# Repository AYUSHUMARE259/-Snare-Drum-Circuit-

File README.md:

# Snare Drum Circuit — PCB Design (EE 322 AMSC Project)

**Course:** EE 322 – Analog and Mixed Signal Circuits
**Term:** Semester 1, 2025–26
**Team:** Team Behzad

## The Team

| Member | Roll No. |
|---|---|
| Yash Sonone | 23110318 |
| Sumedh Wankhede | 23110364 |
| Ayush Umare | 23110346 |

---

## What This Project Is

An electronic snare drum circuit, designed from schematic to soldered board and demonstrated live. The circuit synthesizes a snare-drum sound purely through analog circuitry — no samples, no microcontroller — and the final PCB played back an audible, recognizable snare hit.

Everything here was built the way a real hardware project should be: simulate first, prove it on a breadboard, then commit to copper.

## How We Got There

1. **Simulate** — Modeled the snare drum circuit in LTspice to confirm the topology would actually produce a snare-like waveform before touching hardware.
2. **Prototype** — Built the circuit on a breadboard to validate it worked with real components and real noise, not just an idealized simulation.
3. **Design the PCB** — Captured the schematic in KiCad, assigned footprints, ran ERC to catch wiring issues, then placed and routed the layout.
4. **Verify** — Ran DRC to check the layout against fabrication constraints, and reviewed the board in 3D before export.
5. **Fabricate** — Generated Gerber and drill files and sent them to LionsCircuit for manufacturing.
6. **Build & Demo** — Hand-soldered every component onto the fabricated board and demonstrated the finished circuit producing live snare drum audio.

---

## Repository Layout

```
├── Team_Behzad_Project_Proposal            # project proposal
├── full_schematic_kicad.kicad_pcb_final.kicad_pcb   # PCB layout (KiCad)
├── full_schematic_kicad.kicad_pcb_final.kicad_pro   # KiCad project file
├── gerber_files_amsc_project/                        # Fabrication-ready Gerbers
│   ├── *-F_Cu.gbr / *-B_Cu.gbr            # Copper layers (front/back)
│   ├── *-F_Mask.gbr / *-B_Mask.gbr        # Solder mask layers
│   ├── *-F_Silkscreen.gbr / *-B_Silkscreen.gbr  # Silkscreen layers
│   ├── *-Edge_Cuts.gbr                    # Board outline
│   ├── *-PTH.drl / *-NPTH.drl             # Drill files (plated/non-plated)
│   └── *-job.gbrjob                       # Gerber job file
└── Team Behzad_AMSC.pdf                              # Full written report
```

---

## Toolchain

- **LTspice** — pre-layout circuit simulation
- **KiCad** (v7+ recommended) — schematic capture and PCB layout
- **LionsCircuit** — PCB fabrication

## Getting the Project Running Locally

1. Install [KiCad](https://www.kicad.org/) (v7 or newer).
2. Clone the repo:
   ```bash
   git clone https://github.com/YOUR_USERNAME/Team-Behzad-AMSC.git
   ```
3. Open `full_schematic_kicad.kicad_pcb_final.kicad_pro` in KiCad to view the schematic and layout.

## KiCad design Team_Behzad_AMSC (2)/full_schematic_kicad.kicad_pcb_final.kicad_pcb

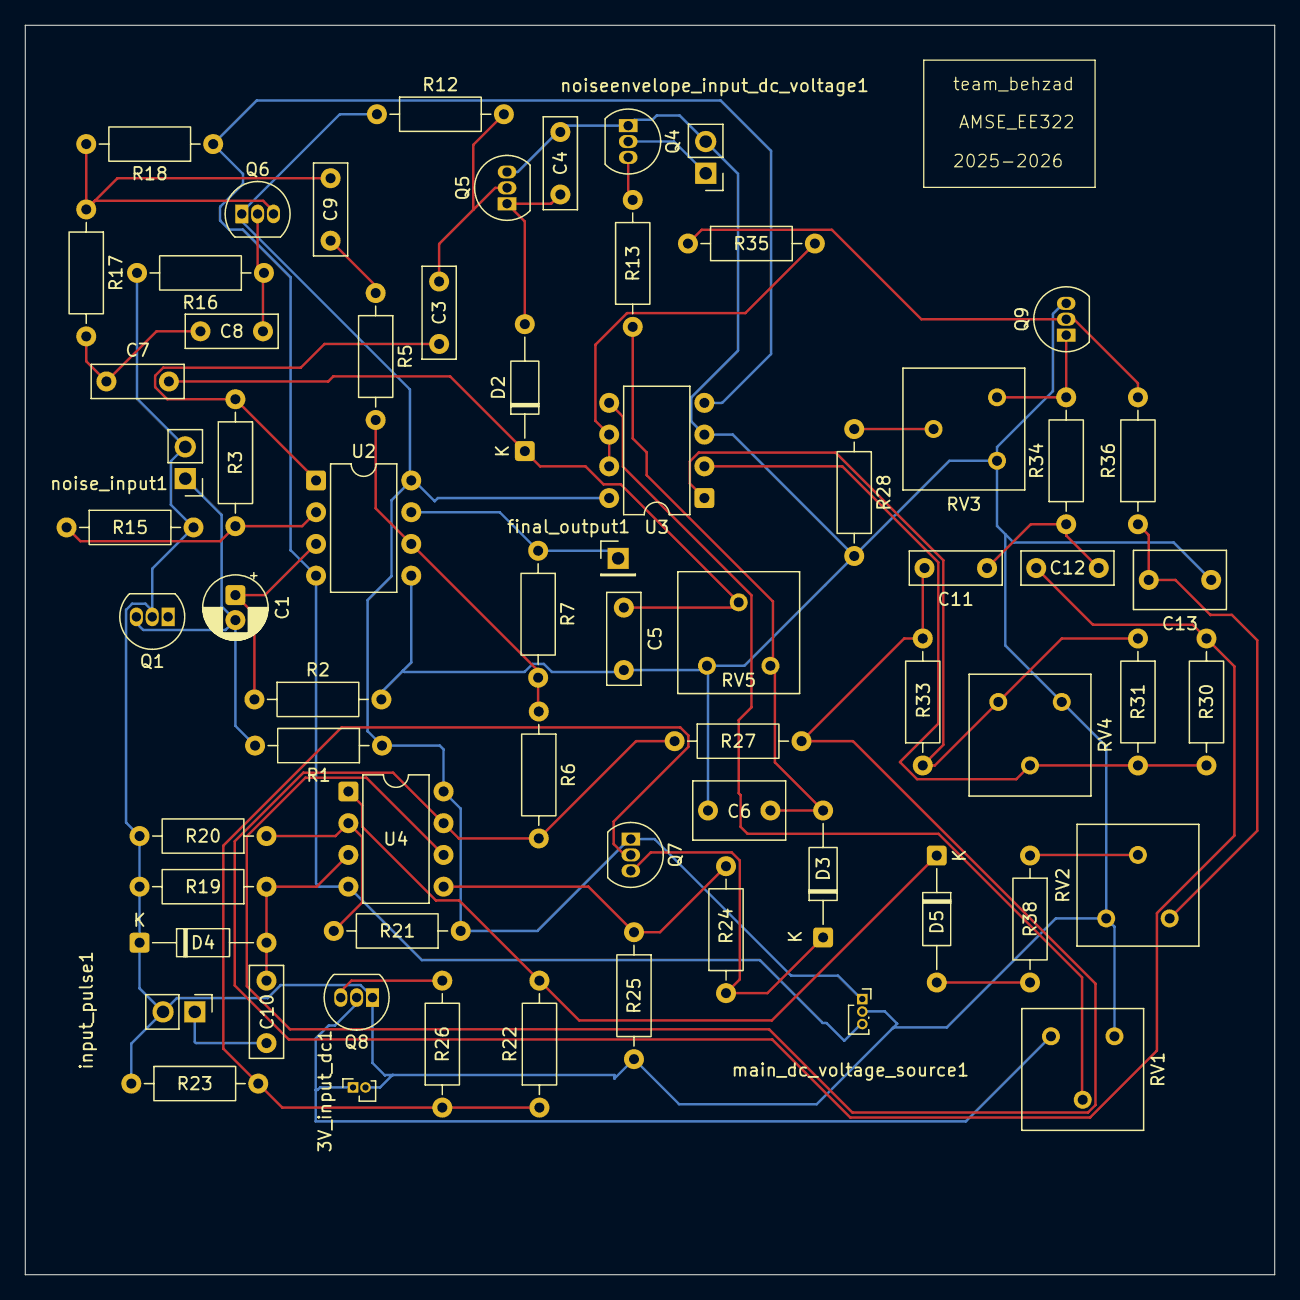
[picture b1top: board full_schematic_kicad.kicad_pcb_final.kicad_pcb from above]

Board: 2 copper layers, 100.0 x 100.0 mm, 66 parts (0 on the bottom side), 41 nets.

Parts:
3V_input_dc1: Conn_01x02_Socket; PinSocket_1x02_P1.00mm_Vertical
C1: 1µ; CP_Radial_D5.0mm_P2.00mm
C3, C11, C12: 33n; C_Rect_L7.2mm_W2.5mm_P5.00mm_FKS2_FKP2_MKS2_MKP2
C4, C5: 2.2n; C_Rect_L7.2mm_W2.5mm_P5.00mm_FKS2_FKP2_MKS2_MKP2
C6, C13: 470n; C_Rect_L7.2mm_W4.5mm_P5.00mm_FKS2_FKP2_MKS2_MKP2
C7, C8: 1n; C_Rect_L7.2mm_W2.5mm_P5.00mm_FKS2_FKP2_MKS2_MKP2
C9, C10: 10n; C_Rect_L7.2mm_W2.5mm_P5.00mm_FKS2_FKP2_MKS2_MKP2
D2, D3, D4, D5: D; D_DO-35_SOD27_P10.16mm_Horizontal
Q1, Q5, Q6, Q7, Q9: NPN; TO-92_Inline
Q4, Q8: PNP; TO-92_Inline
R1, R2, R6, R16, R21, R22: 100k; R_Axial_DIN0207_L6.3mm_D2.5mm_P10.16mm_Horizontal
R3, R12: 1Meg; R_Axial_DIN0207_L6.3mm_D2.5mm_P10.16mm_Horizontal
R5, R24: 10k; R_Axial_DIN0207_L6.3mm_D2.5mm_P10.16mm_Horizontal
R7, R20: 33k; R_Axial_DIN0207_L6.3mm_D2.5mm_P10.16mm_Horizontal
R13, R15, R17, R18, R26: 22k; R_Axial_DIN0207_L6.3mm_D2.5mm_P10.16mm_Horizontal
R19: 39k; R_Axial_DIN0207_L6.3mm_D2.5mm_P10.16mm_Horizontal
R23: 120k; R_Axial_DIN0207_L6.3mm_D2.5mm_P10.16mm_Horizontal
R25, R38: 1k; R_Axial_DIN0207_L6.3mm_D2.5mm_P10.16mm_Horizontal
R27: 910k; R_Axial_DIN0207_L6.3mm_D2.5mm_P10.16mm_Horizontal
R28: 470; R_Axial_DIN0207_L6.3mm_D2.5mm_P10.16mm_Horizontal
R30, R31, R35: 47k; R_Axial_DIN0207_L6.3mm_D2.5mm_P10.16mm_Horizontal
R33: 470k; R_Axial_DIN0207_L6.3mm_D2.5mm_P10.16mm_Horizontal
R34: 330; R_Axial_DIN0207_L6.3mm_D2.5mm_P10.16mm_Horizontal
R36: 27k; R_Axial_DIN0207_L6.3mm_D2.5mm_P10.16mm_Horizontal
RV1, RV2, RV3, RV4, RV5: R_Potentiometer; Potentiometer_Bourns_3386F_Vertical
U2, U3, U4: TL072; DIP-8_W7.62mm
final_output1: Conn_01x01_Socket; PinHeader_1x01_P2.54mm_Vertical
input_pulse1: Conn_01x02_Socket; PinHeader_1x02_P2.54mm_Vertical
main_dc_voltage_source1: Conn_01x03_Socket; PinSocket_1x03_P1.00mm_Vertical
noise_input1: Conn_01x02_Socket; PinHeader_1x02_P2.54mm_Vertical
noiseenvelope_input_dc_voltage1: Conn_01x02_Socket; PinHeader_1x02_P2.54mm_Vertical

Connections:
0: 3V_input_dc1.2, C4.1, C5.2, C6.2, C13.1, D4.1 (+), Q1.2 (B), Q4.1 (C), Q5.3 (E), Q8.1 (C), Q9.3 (E), R2.2, R15.2, R16.2, R19.2, R20.2, R23.1, R25.2, R28.2, RV1.3, RV2.3, RV3.3, RV4.3, RV5.3, U2.5 (+), U3.3 (+), input_pulse1.2, main_dc_voltage_source1.2, noise_input1.2, noiseenvelope_input_dc_voltage1.2
/3v: 3V_input_dc1.1, Q8.2 (B), RV1.1
/-vdd: R18.1, U2.4 (V-), U3.4 (V-), U4.4 (V-), main_dc_voltage_source1.3
/vdd: Q6.1 (C), Q7.1 (C), R1.1, R12.1, R21.1, U2.8 (V+), U3.8 (V+), U4.8 (V+), main_dc_voltage_source1.1
unnamed: C3.2, R3.1, U2.1
unnamed: C7.1, C8.2, R17.2
unnamed: C9.1, R5.1
unnamed: C11.1, C12.2, R34.1
unnamed: C12.1, R6.2, R27.1, R30.2, U4.7
unnamed: C13.2, R36.1, RV2.1
unnamed: C5.1, C7.2, D2.1 (+), RV5.2
unnamed: C4.2, D2.2 (-), Q5.1 (C)
unnamed: D3.1 (+), Q7.3 (E), R24.1
unnamed: C6.1, D3.2 (-), R13.1, RV5.1
unnamed: C10.1, D4.2 (-), R19.1, U4.3 (+)
unnamed: D5.1 (+), R22.2, U4.1
unnamed: D5.2 (-), R38.2
unnamed: C1.2, Q1.3 (E), R1.2, noise_input1.1
unnamed: Q4.2 (B), noiseenvelope_input_dc_voltage1.1
unnamed: Q4.3 (E), R13.2
unnamed: C3.1, Q5.2 (B), R12.2
unnamed: C8.1, Q6.2 (B), R16.1
unnamed: C9.2, Q6.3 (E), R17.1, R18.2
unnamed: Q7.2 (B), R22.1, R23.2, R26.1
unnamed: Q8.3 (E), R26.2
unnamed: Q9.2 (B), R35.1, R36.2
unnamed: Q9.1 (C), R34.2, RV3.1
unnamed: R28.1, RV3.2
unnamed: R31.1, R33.1, RV4.1, U3.1
unnamed: R38.1, RV2.2
unnamed: C1.1, R2.1, U2.3 (+)
unnamed: R3.2, R15.1, U2.2 (-)
unnamed: R5.2, R6.1, R7.2, U2.6 (-)
unnamed: R30.1, R31.2, RV4.2, U3.2 (-)
unnamed: RV1.2, U3.5 (+)
unnamed: R35.2, U3.6 (-), U3.7
unnamed: R20.1, R21.2, U4.2 (-)
unnamed: R24.2, R25.1, U4.5 (+)
unnamed: C11.2, R27.2, R33.2, U4.6 (-)
unnamed: R7.1, U2.7, final_output1.1
unnamed: C10.2, input_pulse1.1
